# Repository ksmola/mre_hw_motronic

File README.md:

# MRE interface board for Motronic 1.3 ECU

Files in KiCAD 5.x format

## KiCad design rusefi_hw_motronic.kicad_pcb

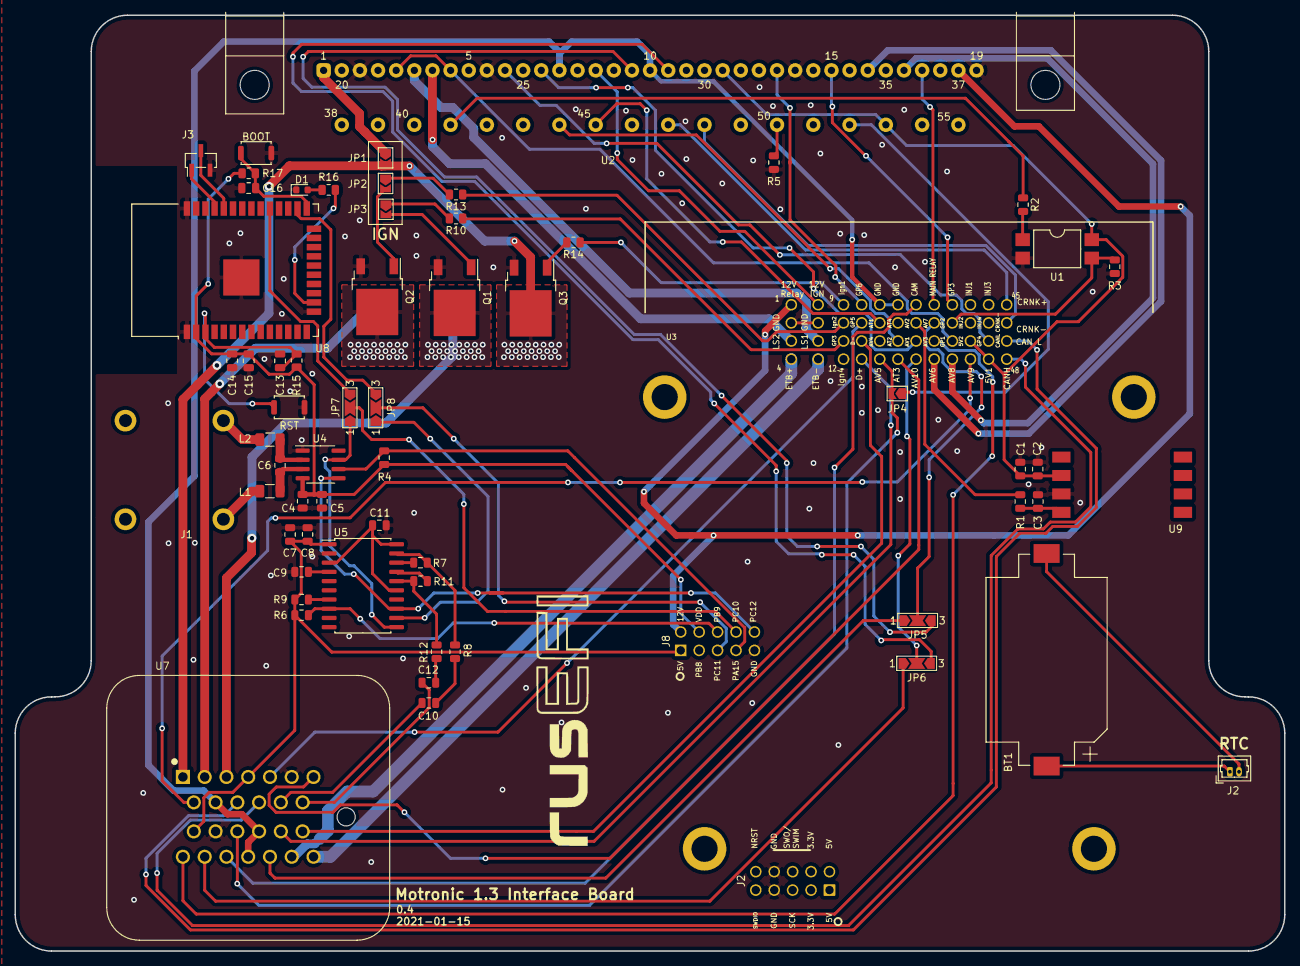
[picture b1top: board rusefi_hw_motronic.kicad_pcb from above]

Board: 2 copper layers, 175.0 x 129.0 mm, 61 parts (0 on the bottom side), 89 nets.

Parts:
BOOT: BOOT; SW_Push_SPST_NO_Alps_SKRK
BT1: Battery_Cell; BatteryHolder_Keystone_1060_1x2032
C1: 1uF; C_0805_2012Metric
C2: 0.01uF; C_0805_2012Metric
C3: 470pF; C_0805_2012Metric
C4, C13, C14, C16: 0.1uF; C_0805_2012Metric
C5, C15: 10uF; C_0805_2012Metric
C6: 10nF; C_0805_2012Metric
C7: 4.7uF; C_0805_2012Metric
C8, C9, C11: 100nF; C_0805_2012Metric
C10, C12: 3.3nF; C_0805_2012Metric
D1: LED; LED_0603_1608Metric
J1: OMEGA PCC_SMP_K; PCC-SMP-MIN
J2: Conn_01x02_Female; Molex_PicoBlade_53047-0210_1x02_P1.25mm_Vertical
J3: Conn_01x03_Male; PinSocket_1x03_P1.27mm_Vertical_SMD_Pin1Left
JP1, JP2, JP3, JP4: SolderJumper; SolderJumper-2_P1.3mm_Open_TrianglePad1.0x1.5mm
JP5, JP6, JP7, JP8: SolderJumper_3_Open; SolderJumper-3_P2.0mm_Open_TrianglePad1.0x1.5mm_NumberLabels
L1, L2: 470 Ohm; L_1206_3216Metric
Q1, Q2, Q3: Q_NIGBT_CEG; TO-252-2
R1: 750; R_0805_2012Metric
R2, R3, R5: 1K; R_0805_2012Metric
R4, R6, R15, R17: 10K; R_0805_2012Metric
R7, R8, R11, R12: 39K; R_0805_2012Metric
R9: 5K; R_0805_2012Metric
R10, R13, R14: 220; R_0805_2012Metric
R16: 100; R_0805_2012Metric
RST: RESET; SW_Push_SPST_NO_Alps_SKRK
U1: SFH617A-2X009T; SMDIP-4_W9.53mm
U2: BOSCH_55P; TE_963063-2
U3: molex_48pin_MRE; Molex_48_MRE
U4: MAX31855KASA; SOIC-8_3.9x4.9mm_P1.27mm
U5: TPIC8101; SOIC-20W_7.5x12.8mm_P1.27mm
U7: TE_6437288-6
U8: ESP32-WROOM-32
U9: MPXA6400A; MPXA4250A6U

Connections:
+3V3: C4.1, C5.1, C14.1, C15.1, R4.2, R15.2, R17.2, U3.J203, U3.J204, U3.J804, U4.4, U8.2
+5V: C1.1, C2.1, C7.1, C8.1, R6.2, R9.1, U1.4, U2.12, U2.53, U3.39, U3.44, U3.J201, U3.J202, U3.J801, U5.1, U7.4, U7.14, U9.2
+12V: U2.37, U3.1, U3.J802
AC_IDLE_IN: R3.1, U1.3, U3.34
AC_ON_INPUT: R2.1, U2.41
AV7: JP5.2, U3.30
AV10: JP6.2, U3.28
BARO: R1.1, U3.26
CAM: U3.25, U7.22
CAN_H: U3.48, U7.11
CAN_L: U3.47, U7.10
CHECK_ENGINE: U2.15, U3.33
CLT: U2.45, U3.18
CS_EGT: R4.1, U3.J807, U4.6
CS_KNOCK: R6.1, U3.J806, U5.8
ECM_RELAY: U2.36, U3.29
ECON: U2.32, U3.13
ETB+: U3.4, U7.25
ETB-: U3.8, U7.26
FAN_PWM: U3.14, U7.5
FUEL_PUMP: U2.3, U2.23, U3.35
GND: BOOT.2, C1.2, C2.2, C3.2, C4.2, C5.2, C7.2, C8.2, C9.2, C11.2, C13.2, C14.2, C15.2, C16.2, D1.1, J3.3, Q1.3, Q2.3, Q3.3, R3.2, R5.2, RST.2, U1.2, U2.2, U2.14, U2.19, U2.24, U3.2, U3.6, U3.J207, U3.J208, U3.J809, U4.1, U5.2, U7.6, U7.15, U8.1, U8.15, U8.38, U8.39, U9.3
IAC_CLOSE: U2.22, U3.7
IAC_OPEN: U2.4, U3.3
IAT: U2.44, U3.23
IGN1: JP1.2, Q3.2, U7.1
IGN2: Q2.2, U7.2
IGN3: Q1.2, U7.3
IGN_A: R14.1, U3.9
IGN_B: R13.1, U3.10
IGN_C: R10.1, U3.11
IGN_SWITCH: U2.27, U3.5
INJ_1: U2.16, U3.32
INJ_2: U2.17, U3.36
KNOCK_1: C10.2, U7.12
KNOCK_2: C12.2, U7.13
MAP: U2.7, U3.27
MISO: JP7.1, U4.7, U5.11
MOSI: JP8.1, U5.12
unnamed: C3.1, R1.2, U9.4
unnamed: C6.1, L1.1, U4.3
unnamed: C6.2, L2.1, U4.2
unnamed: C9.1, U5.4
unnamed: C10.1, R8.2
unnamed: C11.1, U5.3, U5.15, U5.20
unnamed: C12.1, R12.2
unnamed: C13.1, R15.1, RST.1, U8.3
unnamed: BOOT.1, C16.1, R17.1, U8.25
unnamed: D1.2, R16.2
unnamed: J1.1, L1.2
unnamed: J1.2, L2.2
unnamed: JP1.1, U2.1
unnamed: JP2.1, R13.2
unnamed: JP2.2, Q2.1
unnamed: JP3.1, R10.2
unnamed: JP3.2, Q1.1
unnamed: JP4.1, U2.52
unnamed: Q3.1, R14.2
unnamed: R2.2, U1.1
unnamed: R5.1, U2.50
unnamed: R7.1, U5.18
unnamed: R7.2, R8.1, U5.19
unnamed: R9.2, U5.7
unnamed: R11.1, U5.17
unnamed: R11.2, R12.1, U5.16
unnamed: R16.1, U8.16
O2_IN: JP5.3, U2.28
OIL_PRESSURE: U3.40, U7.8
OIL_TEMP: U3.24, U7.7
PC10: JP7.2, U3.J808
PC11: JP8.2, U3.J805
PPS1: U3.31, U7.20
PPS2: JP6.1, U7.21
RTC_BATT+: BT1.1, J2.1
RTC_BATT-: BT1.2, J2.2
RX: J3.2, U8.34
SCK: U3.J810, U4.5, U5.13
SENSOR_GND: U2.10, U2.26, U3.17, U3.21, U7.9, U7.17, U7.23
TACH_OUT: U2.6, U3.43
TPS1: JP4.2, U3.20, U7.16
TPS2: JP5.1, U7.24
TS_WIFI_RX: JP8.3, U8.26
TS_WIFI_TX: JP7.3, U8.29
TX: J3.1, U8.35
USB+: U3.16, U7.18
USB-: U3.15, U7.19
VEHICLE_SPEED: JP6.3, U2.29
VR_N: U2.48, U3.46
VR_P: U2.47, U3.45

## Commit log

2020-07-02 added more parts
2020-07-03 knock knock ...
2020-07-04 cleaned up
2020-07-06 updated injection
2020-07-08 more knock
2020-07-08 more schematics
2020-07-08 more spi stuff
2020-07-09 almost done w schematics
2020-07-10 might be done with schematics
2020-07-11 added footprints
2020-07-11 aaand we have a layout...
2020-07-11 more updates
2020-07-12 started routing
2020-07-13 finished routing
2020-07-14 added rusefi logo
2020-07-14 updated etb traces
2020-07-15 more layout updates
2020-07-15 improved routing
2020-07-15 added bom
2020-07-16 updated BOM
2020-07-16 added gerbers
2020-07-26 v0.2
2020-07-27 updated gnd pour
2020-09-07 new pcb outline
2020-09-08 getting closer...
2020-09-16 finished routing first pass
2020-09-18 cleaned up routing
2020-09-19 added BOM and zipped gerbers
2020-11-07 added PPS pins
2020-11-07 added secondary TPS pins
2020-11-07 added etb sensor pins to layout
2020-11-29 esp32 schematics
2020-12-03 board cleanup
2020-12-03 updated layout for esp32
2021-01-11 added igbts
2021-01-12 routed ignitors
2021-01-16 more routing, getting closer to fab
2021-01-16 fab v0.4
2021-01-18 added readme
2021-01-30 fixed gnd issues
